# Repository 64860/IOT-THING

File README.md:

# ⚙️ IOT-THING

<div align="center">

<!-- TODO: Add a project logo if available in `Images/` or a custom design -->
<!--  -->

**A custom, compact 4-layer PCB design centered around the ESP32-WROOM-32 for robust IoT applications.**

</div>

## 📖 Overview

This project presents the comprehensive design files for a custom, compact 4-layer Printed Circuit Board (PCB). Engineered around the versatile ESP32-WROOM-32 microcontroller, this board is purpose-built for reliable performance in diverse IoT environments. It integrates advanced power management, industrial-grade switching capabilities, and high-speed USB communication, making it an ideal foundation for sophisticated embedded solutions. The design prioritizes compactness, robustness, and efficient signal routing inherent to its 4-layer construction.

## ✨ Key Features

*   **Custom 4-Layer PCB Design:** Optimized for component density, signal integrity, and reduced electromagnetic interference (EMI).
*   **ESP32-WROOM-32 Integration:** Leverages the powerful and feature-rich ESP32 for Wi-Fi, Bluetooth, and extensive I/O capabilities.
*   **Robust Power Management:** Designed for stable power delivery in varying operational conditions, accommodating industrial use cases.
*   **Industrial Switching Capabilities:** Incorporates circuitry for reliable switching of external loads, suitable for automation and control applications.
*   **High-Speed USB Communication:** Provides a fast and reliable interface for programming, debugging, and data exchange.
*   **Compact Form Factor:** Engineered for applications where space is at a premium without compromising functionality.

## 🛠️ Technology Stack

*   **EDA Software:** KiCad (v7 or later recommended)
*   **Microcontroller:** Espressif ESP32-WROOM-32 module
*   **Connectivity:** USB 2.0
*   **PCB Design:** 4-layer stackup

## 🖥️ Visuals

The `Images/` directory contains visual representations of the PCB, including renders, layout screenshots, or schematic snippets. The `3D models/` directory may contain 3D models of the board or specific components, useful for enclosure design or visualization.

<!-- TODO: Add actual screenshots from the `Images` directory, e.g.:

-->

## 🚀 Getting Started

To explore or modify this PCB design, you will need the KiCad EDA Suite.

### Prerequisites

*   **KiCad EDA Suite**: Version 7.0 or newer is recommended for full compatibility with the project files.
    *   [Download KiCad](https://www.kicad.org/download/)

### Installation

1.  **Clone the repository**:
    ```bash
    git clone https://github.com/64860/IOT-THING.git
    cd IOT-THING
    ```

### Opening the Project

1.  **Launch KiCad.**
2.  From the KiCad project manager, go to `File` > `Open Project...` and navigate to the cloned repository.
3.  Select the `IOT_thing.kicad_pro` file and click `Open`.

This will load the entire project, including the schematic (`.kicad_sch`) and PCB layout (`.kicad_pcb`).

### Generating Fabrication Files

Once you have opened the project in KiCad, you can generate manufacturing output files:

1.  **Generate Gerbers for PCB manufacturing:**
    *   Open the `IOT_thing.kicad_pcb` file.
    *   Go to `File` > `Fabrication Outputs` > `Gerber files...`
    *   Configure output settings as required by your PCB manufacturer and click `Plot`.
2.  **Generate Bill of Materials (BOM):**
    *   Open the `IOT_thing.kicad_sch` file.
    *   Go to `Tools` > `Generate Bill of Materials...`
    *   Select a BOM generator script (e.g., `bom_csv_grouped_by_value.py`) and click `Generate`.
3.  **Generate Pick and Place files:**
    *   Open the `IOT_thing.kicad_pcb` file.
    *   Go to `File` > `Fabrication Outputs` > `Footprint Position (.pos) files...`
    *   Configure settings for your assembly house and click `Generate File`.

## 📁 Project Structure

```
IOT-THING/
├── 3D models/                  # 3D models of components or the board, useful for enclosure design.
├── IOT_thing-backups/          # Automatic backup files generated by KiCad.
├── Images/                     # Renders, photos, or diagrams related to the PCB design.
├── IOT_thing.kicad_pcb         # The main KiCad PCB layout file.
├── IOT_thing.kicad_prl         # KiCad project local settings file.
├── IOT_thing.kicad_pro         # The primary KiCad project file (opens the entire project).
├── IOT_thing.kicad_sch         # The main KiCad schematic file.
├── fp-info-cache               # KiCad's footprint information cache.
└── README.md                   # This README file.
```

## 👨‍💻 Firmware Development

This repository focuses on the hardware design. Firmware development for the ESP32-WROOM-32 would typically involve separate software projects using development environments like:

*   **Espressif IDF (ESP-IDF)**: Official IoT Development Framework for ESP32.
*   **Arduino IDE with ESP32 Core**: For easier development using the Arduino ecosystem.
*   **PlatformIO**: A professional embedded development platform.

## 🤝 Contributing

Contributions to improve the PCB design, suggest optimizations, or report issues are welcome! Please feel free to open a GitHub Issue or submit a Pull Request.

## 📄 License

This project currently does not have an explicit license file. Please contact the author for licensing information.

## 🙏 Acknowledgments

*   **KiCad EDA Suite:** For providing a powerful open-source tool for electronics design.
*   **Espressif Systems:** For the ESP32 series of microcontrollers.

## 📞 Support & Contact

-   🐛 Issues: [GitHub Issues](https://github.com/64860/IOT-THING/issues)

---

<div align="center">

**⭐ Star this repo if you find this hardware design helpful or inspiring!**

Made with ❤️ by [64860](https://github.com/64860)

</div>
```

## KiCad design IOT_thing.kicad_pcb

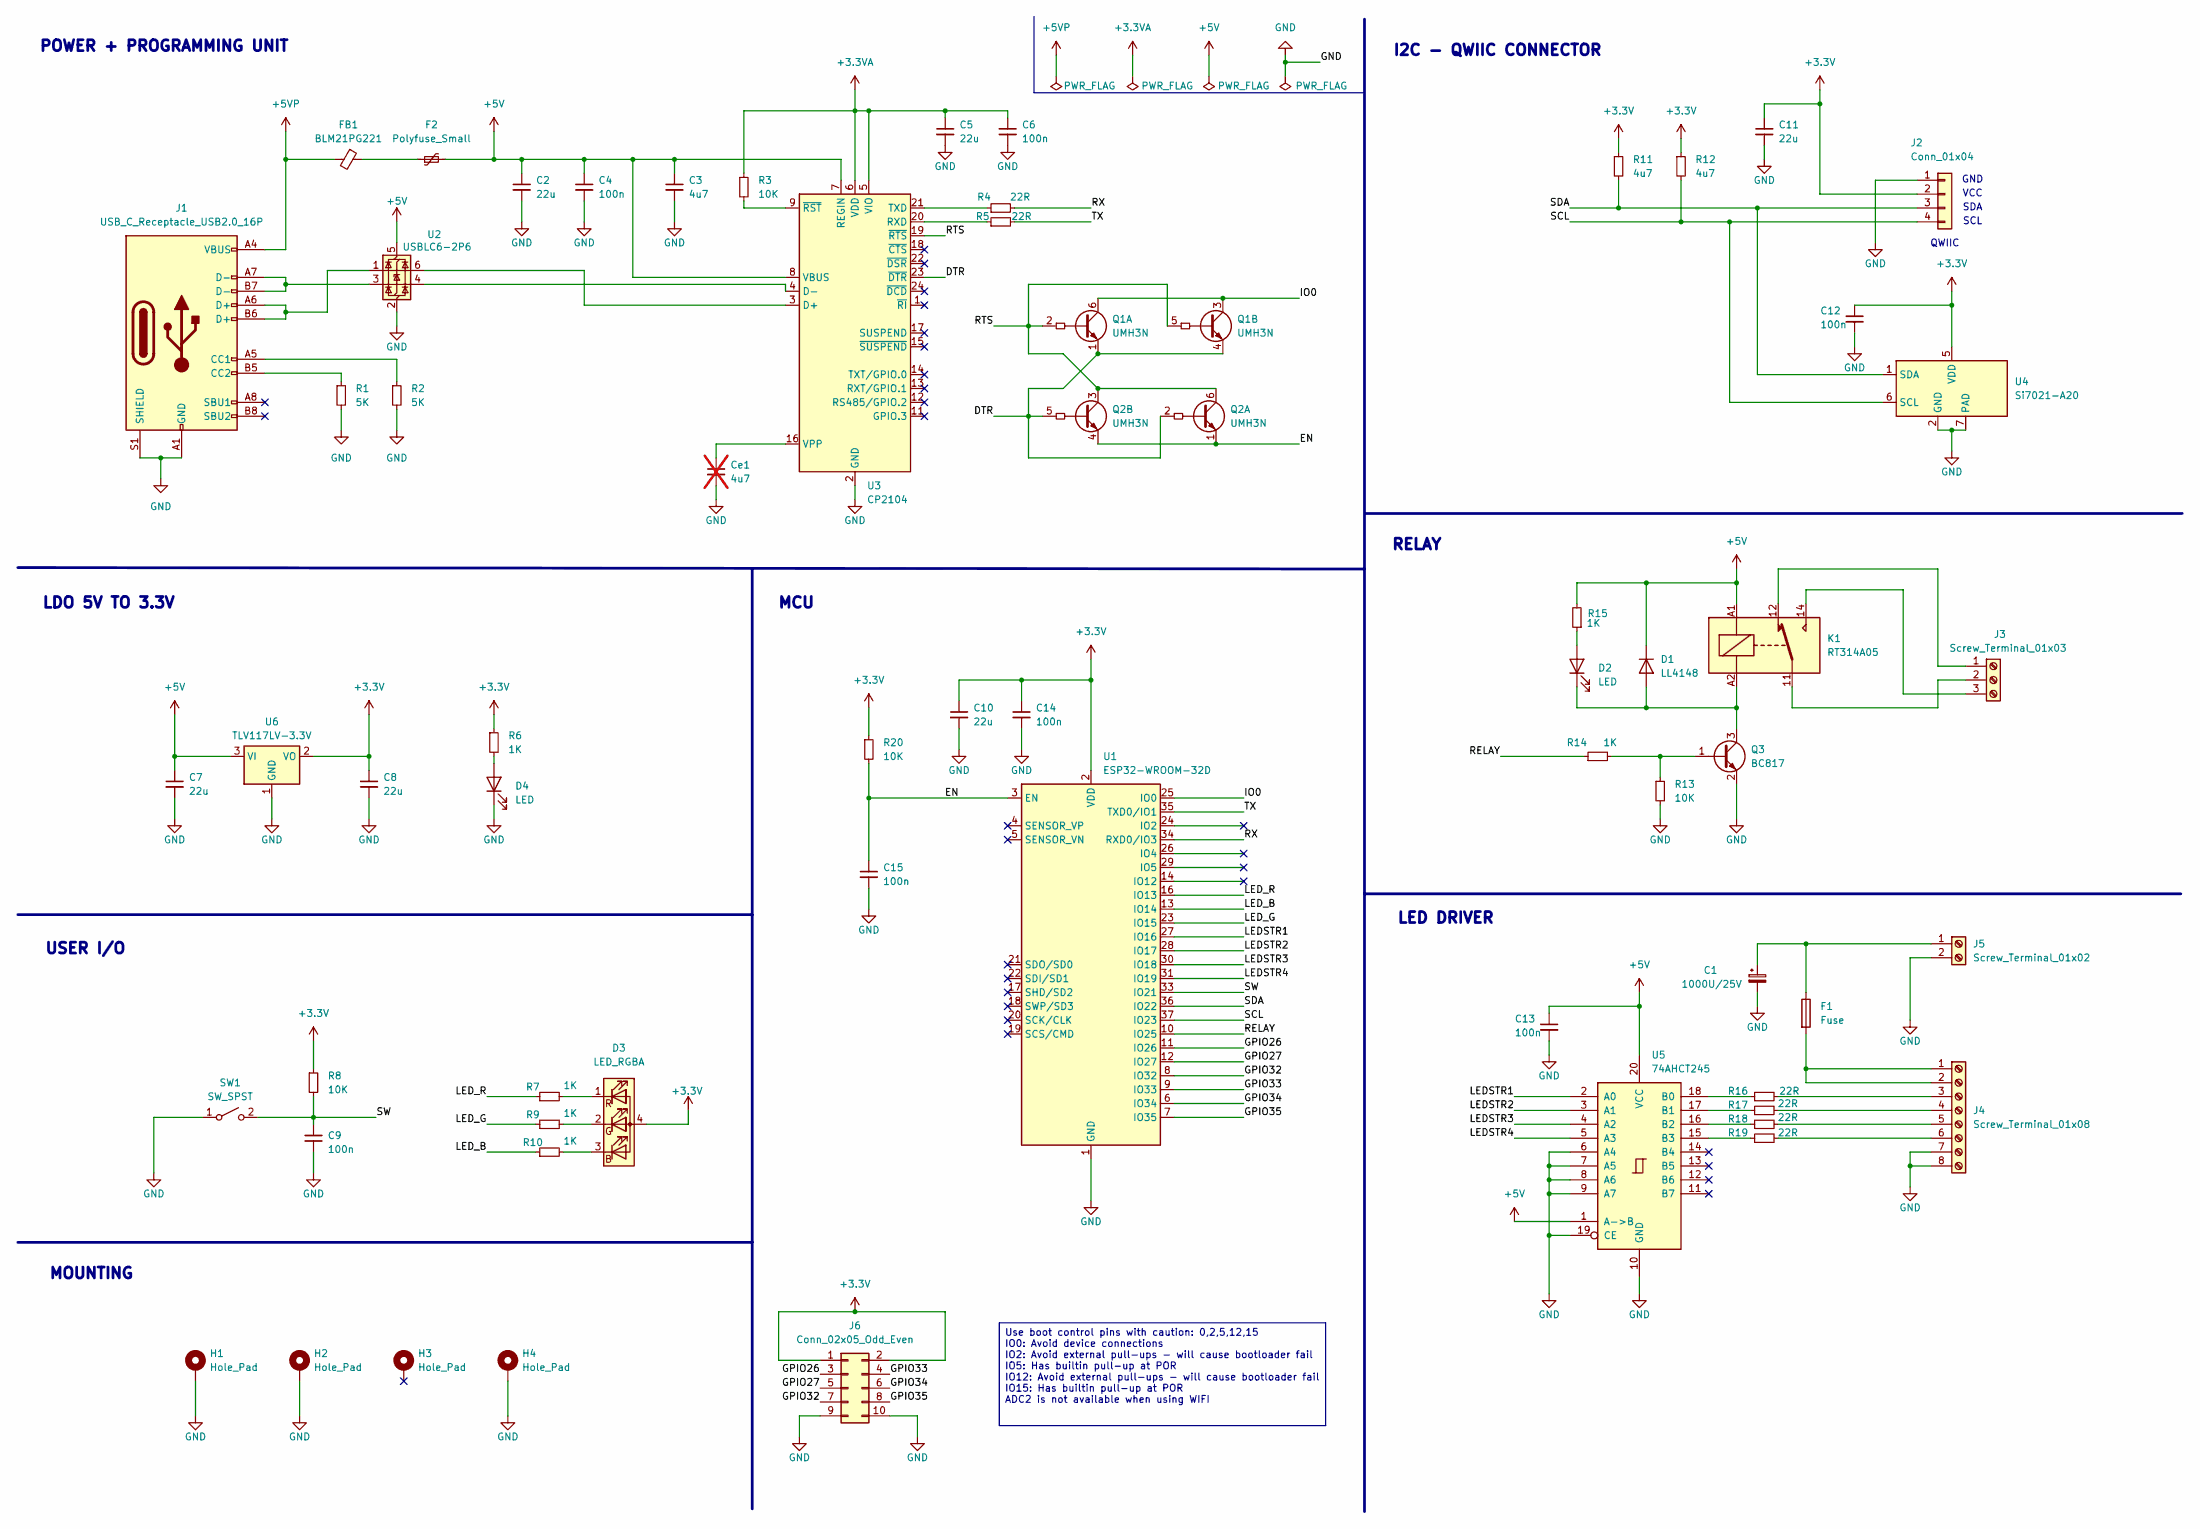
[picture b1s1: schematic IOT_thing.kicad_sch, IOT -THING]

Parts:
C1: 1000U/25V; CP_Radial_D10.0mm_P5.00mm
C2, C5, C7, C8, C10, C11: 22u; C_0805_2012Metric_Pad1.18x1.45mm_HandSolder
C3: 4u7; C_0805_2012Metric_Pad1.18x1.45mm_HandSolder
C4, C6, C9, C12, C13, C14, C15: 100n; C_0402_1005Metric_Pad0.74x0.62mm_HandSolder
Ce1: 4u7; C_0805_2012Metric_Pad1.18x1.45mm_HandSolder; not fitted
D1: LL4148; D_MiniMELF
D2, D4: LED; LED_0603_1608Metric_Pad1.05x0.95mm_HandSolder
D3: LED_RGBA; LED_RGB_Wuerth-PLCC4_3.2x2.8mm_150141M173100
F1: Fuse; FUSE_696105003002
F2: Polyfuse_Small; Fuse_1206_3216Metric_Pad1.42x1.75mm_HandSolder
FB1: BLM21PG221; L_0603_1608Metric_Pad1.05x0.95mm_HandSolder
H1, H2, H3, H4: Hole_Pad; MountingHole_3.2mm_M3_Pad_Via
J1: USB_C_Receptacle_USB2.0_16P; USB_C_Receptacle_HRO_TYPE-C-31-M-12
J2: Conn_01x04; JST_SH_SM04B-SRSS-TB_1x04-1MP_P1.00mm_Horizontal
J3: Screw_Terminal_01x03; TerminalBlock_Phoenix_MKDS-3-3-5.08_1x03_P5.08mm_Horizontal
J4: Screw_Terminal_01x08; TerminalBlock_Phoenix_MKDS-1,5-8_1x08_P5.00mm_Horizontal
J5: Screw_Terminal_01x02; TerminalBlock_Phoenix_MKDS-1,5-2-5.08_1x02_P5.08mm_Horizont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
J6: Conn_02x05_Odd_Even; PinHeader_2x05_P2.54mm_Vertical
K1: RT314A05; Relay_SPDT_Schrack-RT1-16A-FormC_RM5mm
Q1, Q2: UMH3N; SOT-363_SC-70-6
Q3: BC817; SOT-23
R1, R2: 5K; R_0402_1005Metric_Pad0.72x0.64mm_HandSolder
R3, R8, R13, R20: 10K; R_0402_1005Metric_Pad0.72x0.64mm_HandSolder
R4, R5, R16, R17, R18, R19: 22R; R_0402_1005Metric_Pad0.72x0.64mm_HandSolder
R6, R7, R9, R10, R14, R15: 1K; R_0402_1005Metric_Pad0.72x0.64mm_HandSolder
R11, R12: 4u7; R_0402_1005Metric_Pad0.72x0.64mm_HandSolder
SW1: SW_SPST; SW_Push_1P1T_NO_6x6mm_H9.5mm
U1: ESP32-WROOM-32D
U2: USBLC6-2P6; SOT-666
U3: CP2104; QFN-24-1EP_4x4mm_P0.5mm_EP2.6x2.6mm
U4: Si7021-A20; DFN-6-1EP_3x3mm_P1mm_EP1.5x2.4mm
U5: 74AHCT245; DIP-20_W7.62mm
U6: TLV117LV-3.3V; SOT-223-3_TabPin2

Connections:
+3.3V: C8.1, C10.1, C11.1, C12.1, C14.1, D3.4 (A), J2.2, J6.1, J6.2, R6.1, R8.1, R11.1, R12.1, R20.1, U1.2 (VDD), U4.5 (VDD), U6.2 (VO)
+3.3VA: C5.1, C6.1, R3.1, U3.5 (VIO), U3.6 (VDD)
+5V: C2.1, C3.1, C4.1, C7.1, C13.1, D1.1 (K), F2.2, K1.A1, R15.2, U2.5 (VBUS), U3.7 (REGIN), U3.8 (VBUS), U5.1 (A->B), U5.20 (VCC), U6.3 (VI)
+5VP: FB1.2, J1.A4 (VBUS), J1.A9 (VBUS), J1.B4 (VBUS), J1.B9 (VBUS)
/DTR: Q1.1 (E1), Q1.4 (E2), Q2.2 (B1), Q2.5 (B2), U3.23 (~DTR)
/EN: C15.1, Q2.1 (E1), Q2.4 (E2), R20.2, U1.3 (EN)
/GPIO26: J6.3, U1.11 (IO26)
/GPIO27: J6.5, U1.12 (IO27)
/GPIO32: J6.7, U1.8 (IO32)
/GPIO33: J6.4, U1.9 (IO33)
/GPIO34: J6.6, U1.6 (IO34)
/GPIO35: J6.8, U1.7 (IO35)
/IO0: Q1.3 (C2), Q1.6 (C1), U1.25 (IO0)
/LEDSTR1: U1.27 (IO16), U5.2 (A0)
/LEDSTR2: U1.28 (IO17), U5.3 (A1)
/LEDSTR3: U1.30 (IO18), U5.4 (A2)
/LEDSTR4: U1.31 (IO19), U5.5 (A3)
/LED_B: R10.1, U1.13 (IO14)
/LED_G: R9.1, U1.23 (IO15)
/LED_R: R7.1, U1.16 (IO13)
/RELAY: R14.1, U1.10 (IO25)
/RTS: Q1.2 (B1), Q1.5 (B2), Q2.3 (C2), Q2.6 (C1), U3.19 (~RTS)
/RX: R4.2, U1.34 (RXD0/IO3)
/SCL: J2.4, R12.2, U1.37 (IO23), U4.6 (SCL)
/SDA: J2.3, R11.2, U1.36 (IO22), U4.1 (SDA)
/SW: C9.1, R8.2, SW1.2 (B), U1.33 (IO21)
/TX: R5.2, U1.35 (TXD0/IO1)
GND: C1.2, C2.2, C3.2, C4.2, C5.2, C6.2, C7.2, C8.2, C9.2, C10.2, C11.2, C12.2, C13.2, C14.2, C15.2, Ce1.2, D4.1 (K), H1.1, H2.1, H4.1, J1.A1 (GND), J1.A12 (GND), J1.B1 (GND), J1.B12 (GND), J1.S1 (SHIELD), J2.1, J4.7, J4.8, J5.2, J6.9, J6.10, Q3.2 (E), R1.2, R2.2, R13.2, SW1.1 (A), U1.1 (GND), U1.15 (GND), U1.38 (GND), U1.39 (GND), U2.2 (GND), U3.2 (GND), U3.25 (GND), U4.2 (GND), U4.7 (PAD), U5.6 (A4), U5.7 (A5), U5.8 (A6), U5.9 (A7), U5.10 (GND), U5.19 (CE), U6.1 (GND)
unnamed: D1.2 (A), D2.1 (K), K1.A2, Q3.3 (C)
unnamed: D2.2 (A), R15.1
unnamed: D3.3 (BK), R10.2
unnamed: D3.2 (GK), R9.2
unnamed: D3.1 (RK), R7.2
unnamed: D4.2 (A), R6.2
unnamed: F2.1, FB1.1
unnamed: J1.A5 (CC1), R2.1
unnamed: J1.B5 (CC2), R1.1
unnamed: J1.A6 (D+), J1.B6 (D+), U2.1 (I/O1)
unnamed: J1.A7 (D-), J1.B7 (D-), U2.3 (I/O2)
unnamed: J3.1, K1.12
unnamed: J3.2, K1.11
unnamed: J3.3, K1.14
unnamed: F1.2, J4.1, J4.2
unnamed: J4.3, R16.2
unnamed: J4.4, R17.2
unnamed: J4.5, R18.2
unnamed: J4.6, R19.2
unnamed: C1.1, F1.1, J5.1
unnamed: Q3.1 (B), R13.1, R14.2
unnamed: U2.6 (I/O1), U3.3 (D+)
unnamed: U2.4 (I/O2), U3.4 (D-)
unnamed: R5.1, U3.20 (RXD)
unnamed: R4.1, U3.21 (TXD)
unnamed: Ce1.1, U3.16 (VPP)
unnamed: R3.2, U3.9 (~RST)
unnamed: R16.1, U5.18 (B0)
unnamed: R17.1, U5.17 (B1)
unnamed: R18.1, U5.16 (B2)
unnamed: R19.1, U5.15 (B3)

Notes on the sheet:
LED DRIVER
MOUNTING
SDA
GND
LDO 5V TO 3.3V
SCL
RELAY
USER I/O
MCU
QWIIC
POWER + PROGRAMMING UNIT
VCC
I2C - QWIIC CONNECTOR
Use boot control pins with caution: 0,2,5,12,15 IO0: Avoid device connections IO2: Avoid external pull-ups - will cause bootloader fail IO5: Has builtin pull-up at POR IO12: Avoid external pull-ups - will cause bootloader fail IO15: Has builtin pull-up at POR ADC2 is not available when using WIFI

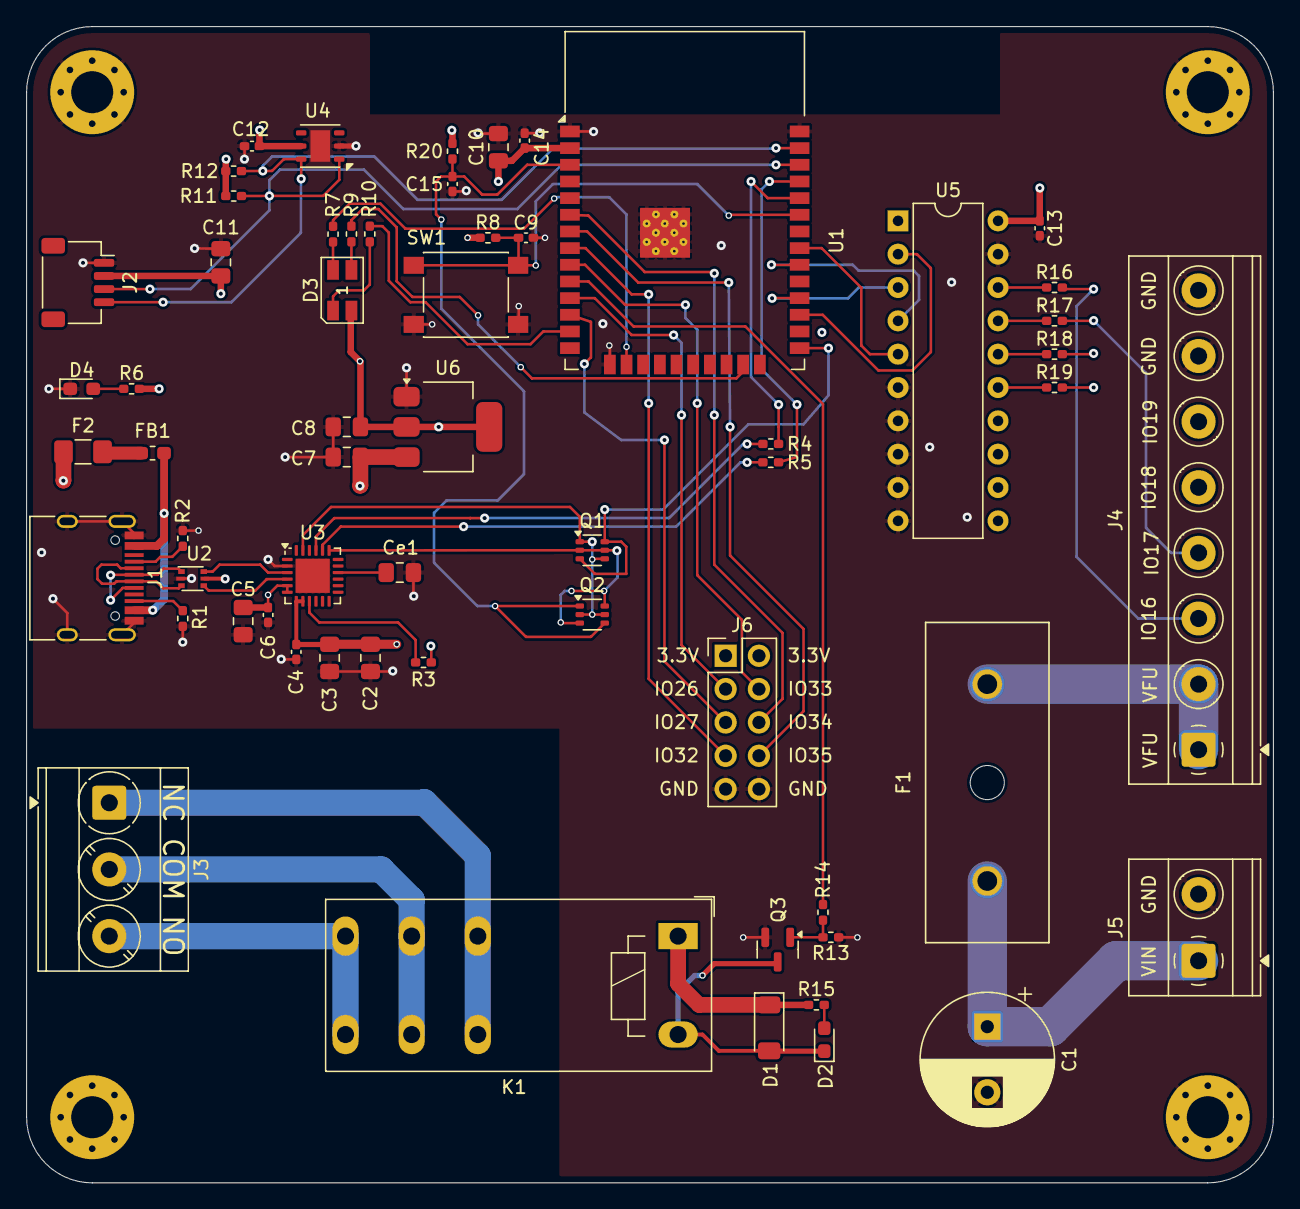
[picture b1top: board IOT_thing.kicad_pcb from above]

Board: 4 copper layers, 95.0 x 88.1 mm, 64 parts (0 on the bottom side), 59 nets.

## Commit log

2025-07-09 Added components
2025-08-12 Placed all components
2025-08-12 Edited the USBC symbol
2025-08-12 Finished wiring the programming interface
2025-08-12 Finished the power supply
2025-08-12 Finished wiring the I2C part
2025-08-12 Finished wiring the relay module
2025-08-12 Finished wiring the ledstrip part
2025-08-14 Completed commenting on the sheet and did annotations
2025-08-25 Completed adding footprints
2025-08-25 Started laying out the components
2025-12-25 Updated some footprints and 3d models
2025-12-25 Finalised updating all the 3d models
2025-12-25 Finished arranging the components
2025-12-26 Arranged the layout and finalised the silkscreen
2025-12-30 Finalised the project
2025-12-30 Add README.md for ESP32-WROOM-32 project
    Added detailed project overview, technical specifications, and repository structure for the ESP32-WROOM-32 Multilayer Control Hub.
2025-12-30 Revise project overview and key features in README
    Updated README.md to enhance project overview and details.
